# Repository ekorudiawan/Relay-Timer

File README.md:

# Relay-Timer
Simple Relay Timer Setting Via Button and LCD

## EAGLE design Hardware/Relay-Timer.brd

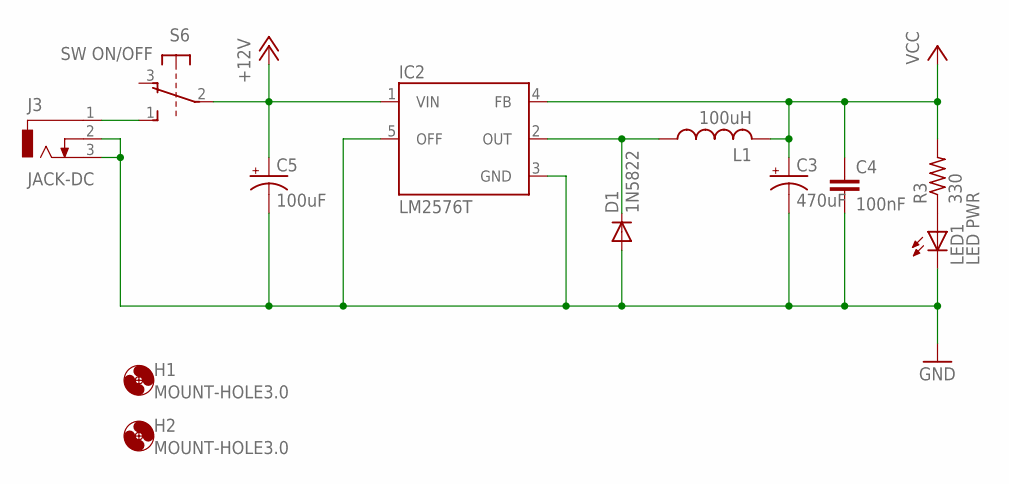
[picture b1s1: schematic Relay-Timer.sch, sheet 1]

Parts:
C3: 470uF; E3,5-8
C4: 100nF; C025-024X044
C5: 100uF; E2,5-6
D1: 1N5822; DO201-15
H1, H2: MOUNT-HOLE3.0; 3,0
IC2: LM2576T; TO220-5
J3: JACK-DC; DCJ0202
L1: 100uH; TJ3-U2
LED1: LED PWR; LED3MM
R3: 330; 0204/7
S6: SW ON/OFF; 9077-2

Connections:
+12V: C5.+, IC2.1 (VIN), S6.2; also elsewhere on the board
GND: C3.-, C4.2, C5.-, D1.A, IC2.3 (GND), IC2.5 (OFF), J3.2, J3.3, LED1.K (C); also elsewhere on the board
unnamed: D1.C, IC2.2 (OUT), L1.1
unnamed: LED1.A, R3.1
unnamed: J3.1, S6.1 (S)
VCC: C3.+, C4.1, IC2.4 (FB), L1.2, R3.2; also elsewhere on the board

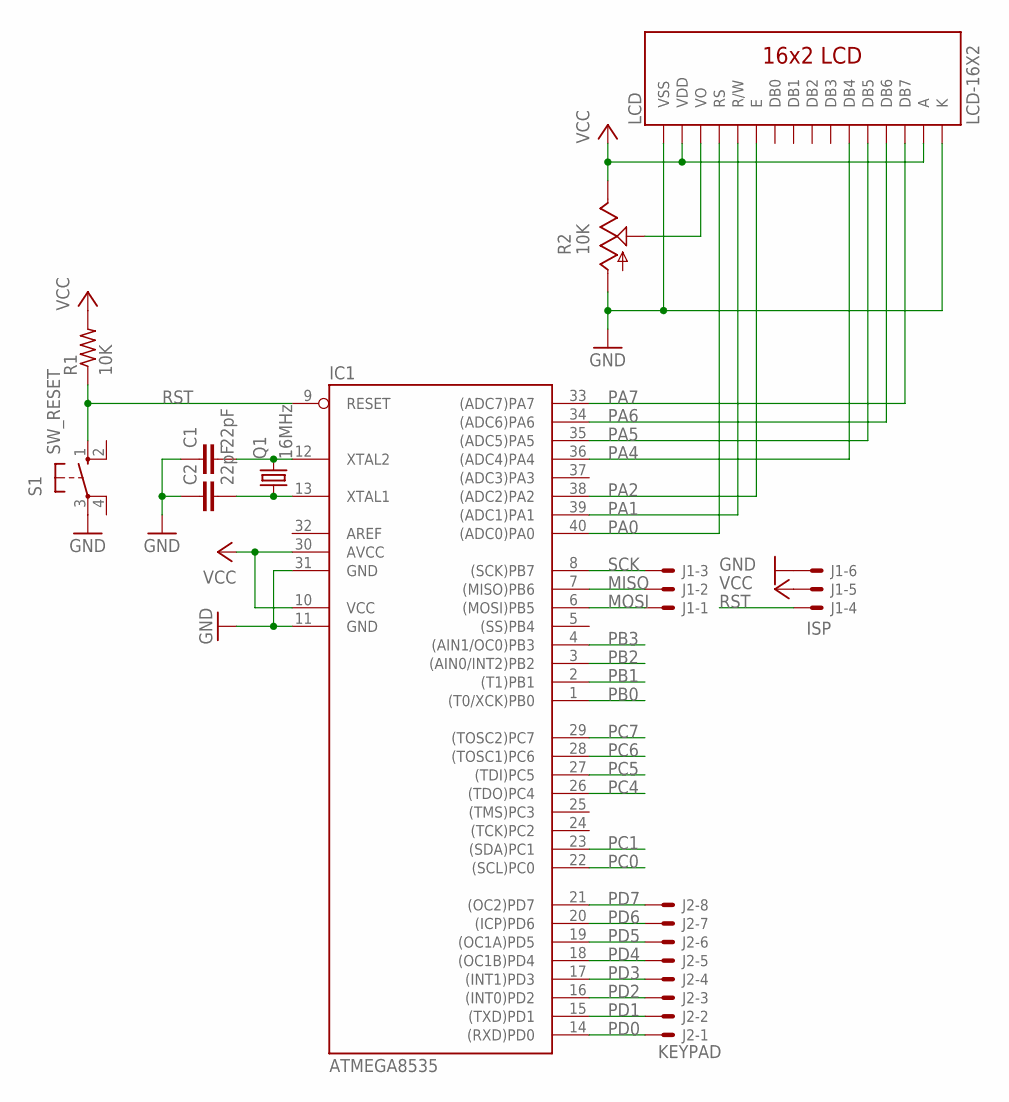
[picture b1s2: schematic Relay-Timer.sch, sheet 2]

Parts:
C1, C2: 22pF; C025-024X044
IC1: ATMEGA8535; DIL40
J1: ISP; 6410-06
J2: KEYPAD; 6410-08
LCD: LCD-16X2
Q1: 16MHz; HC49/S
R1: 10K; 0204/7
R2: 10K; CA6V
S1: SW_RESET; B3F-10XX

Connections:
GND: C1.1, C2.1, IC1.11 (GND), IC1.31 (GND), J1.6, LCD.1 (VSS), LCD.16 (K), R2.A, S1.3; also elsewhere on the board
MISO: IC1.7 ((MISO)PB6), J1.2
MOSI: IC1.6 ((MOSI)PB5), J1.1
unnamed: C1.2, IC1.12 (XTAL2), Q1.2
unnamed: C2.2, IC1.13 (XTAL1), Q1.1
unnamed: LCD.3 (VO), R2.S
PA0: IC1.40 ((ADC0)PA0), LCD.4 (RS)
PA1: IC1.39 ((ADC1)PA1), LCD.5 (R/W)
PA2: IC1.38 ((ADC2)PA2), LCD.6 (E)
PA4: IC1.36 ((ADC4)PA4), LCD.11 (DB4)
PA5: IC1.35 ((ADC5)PA5), LCD.12 (DB5)
PA6: IC1.34 ((ADC6)PA6), LCD.13 (DB6)
PA7: IC1.33 ((ADC7)PA7), LCD.14 (DB7)
PB0: IC1.1 ((T0/XCK)PB0); also elsewhere on the board
PB1: IC1.2 ((T1)PB1); also elsewhere on the board
PB2: IC1.3 ((AIN0/INT2)PB2); also elsewhere on the board
PB3: IC1.4 ((AIN1/OC0)PB3); also elsewhere on the board
PC0: IC1.22 ((SCL)PC0); also elsewhere on the board
PC1: IC1.23 ((SDA)PC1); also elsewhere on the board
PC4: IC1.26 ((TDO)PC4); also elsewhere on the board
PC5: IC1.27 ((TDI)PC5); also elsewhere on the board
PC6: IC1.28 ((TOSC1)PC6); also elsewhere on the board
PC7: IC1.29 ((TOSC2)PC7); also elsewhere on the board
PD0: IC1.14 ((RXD)PD0), J2.1
PD1: IC1.15 ((TXD)PD1), J2.2
PD2: IC1.16 ((INT0)PD2), J2.3
PD3: IC1.17 ((INT1)PD3), J2.4
PD4: IC1.18 ((OC1B)PD4), J2.5
PD5: IC1.19 ((OC1A)PD5), J2.6
PD6: IC1.20 ((ICP)PD6), J2.7
PD7: IC1.21 ((OC2)PD7), J2.8
RST: IC1.9 (RESET), J1.4, R1.1, S1.1 (S)
SCK: IC1.8 ((SCK)PB7), J1.3
VCC: IC1.10 (VCC), IC1.30 (AVCC), J1.5, LCD.2 (VDD), LCD.15 (A), R1.2, R2.E; also elsewhere on the board

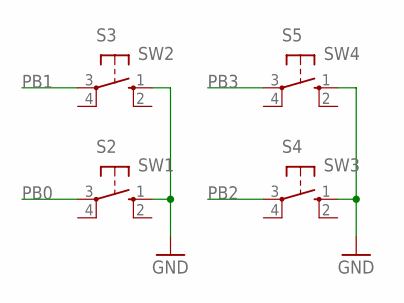
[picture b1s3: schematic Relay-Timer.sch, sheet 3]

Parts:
S2: SW1; B3F-10XX
S3: SW2; B3F-10XX
S4: SW3; B3F-10XX
S5: SW4; B3F-10XX

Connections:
GND: S2.1 (S), S3.1 (S), S4.1 (S), S5.1 (S); also elsewhere on the board
PB0: S2.3; also elsewhere on the board
PB1: S3.3; also elsewhere on the board
PB2: S4.3; also elsewhere on the board
PB3: S5.3; also elsewhere on the board

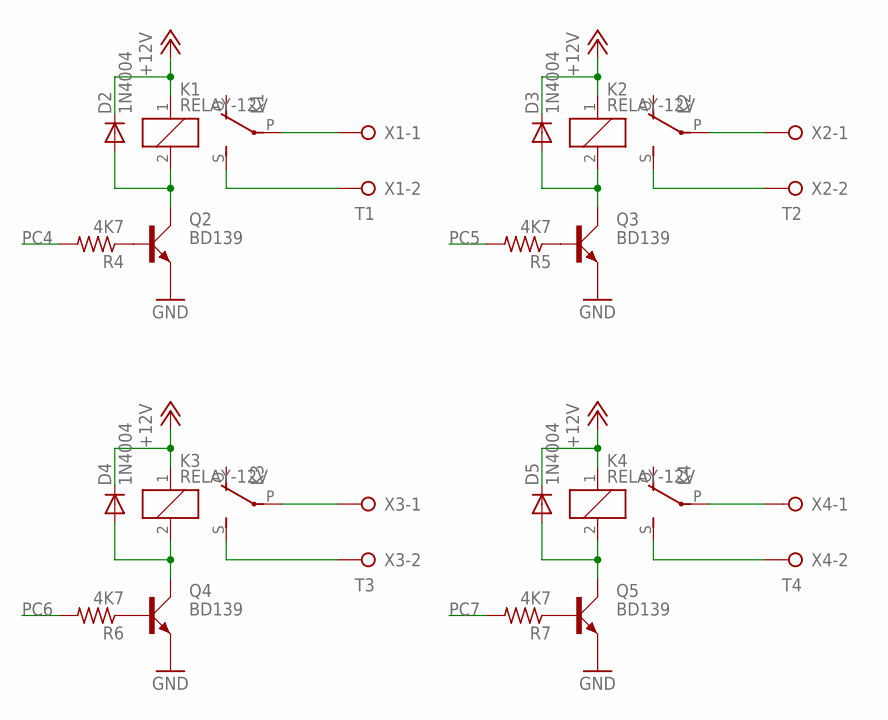
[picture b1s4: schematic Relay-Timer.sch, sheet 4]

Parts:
D2, D3, D4, D5: 1N4004; DO41-10
K1, K2, K3, K4: RELAY-12V; G5LE
Q2, Q3, Q4, Q5: BD139; TO126AV
R4, R5, R6, R7: 4K7; 0204/7
X1: T1; W237-132
X2: T2; W237-132
X3: T3; W237-132
X4: T4; W237-132

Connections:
+12V: D2.C, D3.C, D4.C, D5.C, K1.1, K2.1, K3.1, K4.1; also elsewhere on the board
GND: Q2.E, Q3.E, Q4.E, Q5.E; also elsewhere on the board
unnamed: D2.A, K1.2, Q2.C
unnamed: Q2.B, R4.1
unnamed: K1.P, X1.1
unnamed: K1.S, X1.2
unnamed: D3.A, K2.2, Q3.C
unnamed: Q3.B, R5.1
unnamed: K2.P, X2.1
unnamed: K2.S, X2.2
unnamed: D4.A, K3.2, Q4.C
unnamed: Q4.B, R6.1
unnamed: K3.P, X3.1
unnamed: K3.S, X3.2
unnamed: D5.A, K4.2, Q5.C
unnamed: Q5.B, R7.1
unnamed: K4.P, X4.1
unnamed: K4.S, X4.2
PC4: R4.2; also elsewhere on the board
PC5: R5.2; also elsewhere on the board
PC6: R6.2; also elsewhere on the board
PC7: R7.2; also elsewhere on the board

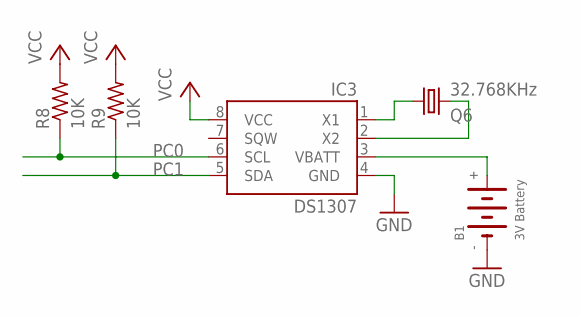
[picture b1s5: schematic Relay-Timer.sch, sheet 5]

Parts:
B1: 3V Battery; CR2032
IC3: DS1307; DIP08
Q6: 32.768KHz; TC26H
R8, R9: 10K; 0204/7

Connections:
GND: B1.-, IC3.4 (GND); also elsewhere on the board
unnamed: IC3.1 (X1), Q6.1
unnamed: IC3.2 (X2), Q6.2
unnamed: B1.+, IC3.3 (VBATT)
PC0: IC3.6 (SCL), R8.1; also elsewhere on the board
PC1: IC3.5 (SDA), R9.1; also elsewhere on the board
VCC: IC3.8 (VCC), R8.2, R9.2; also elsewhere on the board

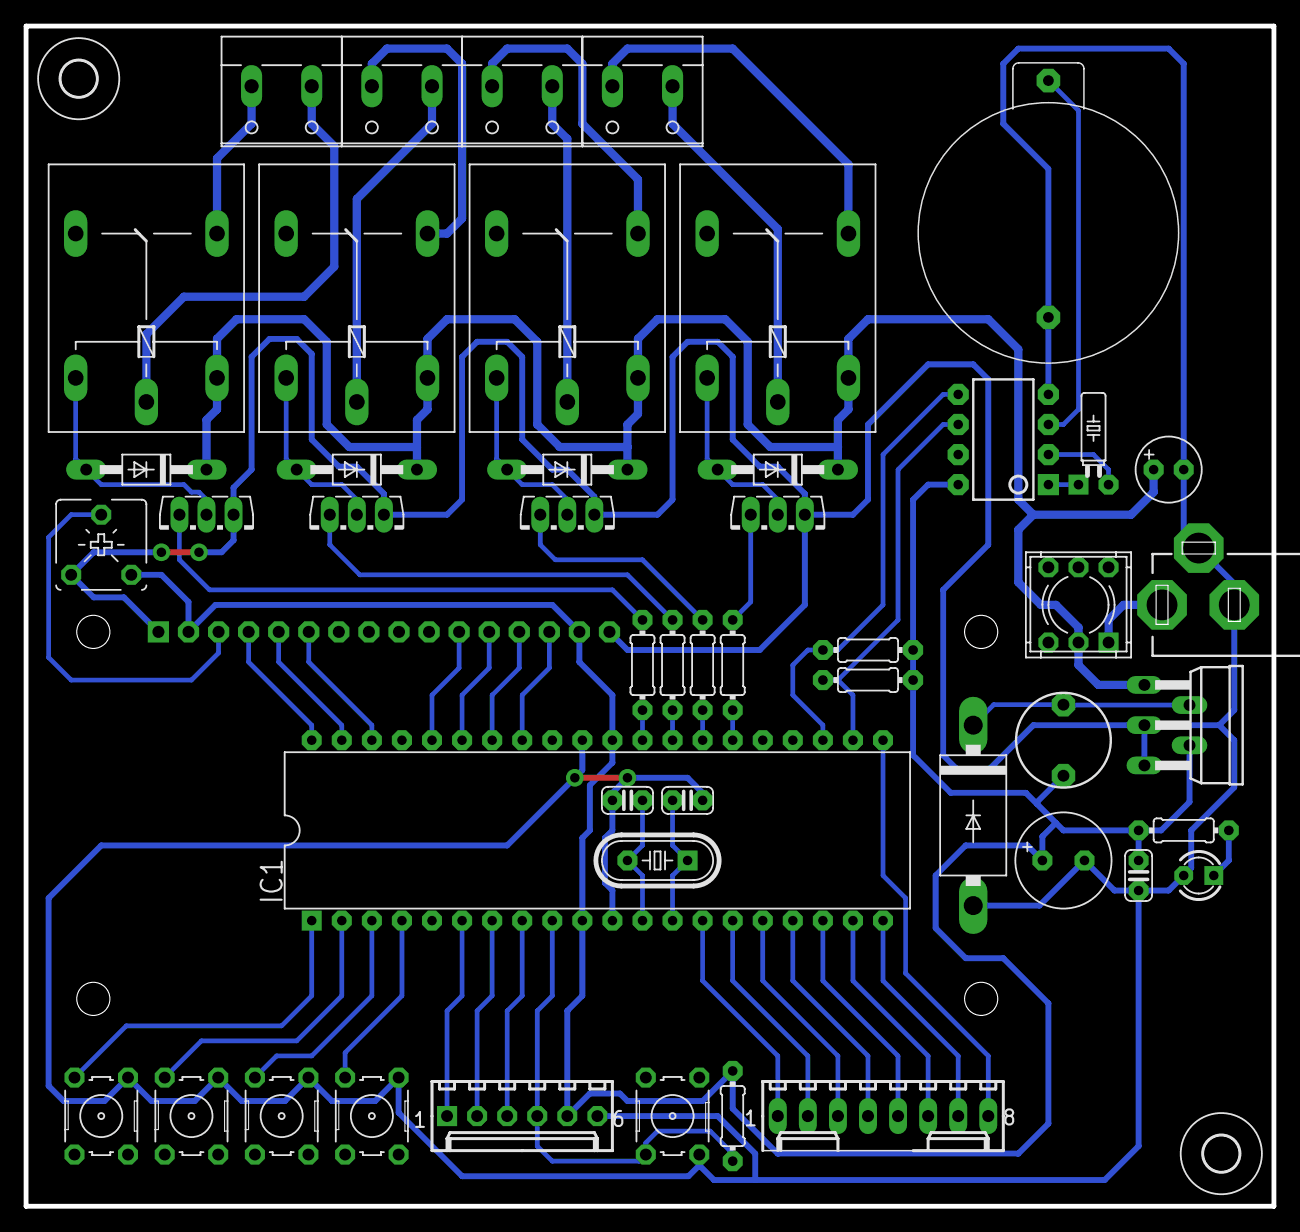
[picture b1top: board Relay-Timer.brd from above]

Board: 2 copper layers, 105.4 x 99.7 mm, 51 parts (0 on the bottom side), 57 nets.

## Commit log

2017-10-03 Added HW & SW source files
